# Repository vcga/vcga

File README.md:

UNTUK SAAT INI HINGGA JANGKA WAKTU YANG BELUM DAPAT DITENTUKAN,
BAHWASANYA VCGA SEBAGAI ANAK CABANG DARI DARI MATRIX 1.4 III,
DALAM MASA "SUSPENDED"
ATAU "DITUTUP SEMENTARA" TERKAIT MASA "SUSPENDED" YANG DIPERLAKUKAN
TERHADAP KESELURUHAN MATRIX 1.4. PENYEDIAAN DUKUNGAN TEKNIKAL, SKEMATIK,
& DOKUMENTASI - DIHENTIKAN.
SKEMATIK & DOKUMENTASI LAINNYA AKAN TERSEDIA KEMBALI JIKA TELAH
DIPUTUSKAN KEADAAN "DIBUKA KEMBALI".

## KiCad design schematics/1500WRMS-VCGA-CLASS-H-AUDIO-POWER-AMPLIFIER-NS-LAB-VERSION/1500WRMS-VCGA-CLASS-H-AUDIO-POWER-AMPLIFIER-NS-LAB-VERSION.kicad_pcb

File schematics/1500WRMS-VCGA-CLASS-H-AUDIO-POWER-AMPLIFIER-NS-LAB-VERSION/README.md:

1500 Watt RMS MATRIX 1.4 III Class-H Audio Power Amplifier Core Circuit
=======================================================================

BASIC TECHNICAL SPECIFICATIONS
------------------------------

Output Power Rating: 1500 watts RMS  
Output Amplitude Rating: 78.4V RMS  
Minimum Output Load Impedance: 4-ohms  
High Rail Power Supply Voltage: 120V DC precision dual-supply  
Low Rail Power Supply Voltage: 42V DC precision dual-supply  
Input: 1V RMS nominal, 10V RMS maximum  

Features:
- Stepper Frequency Limiter to prevent distortion of high frequency amplification
- Soft Signal Limiter
- Fault / Short & Open Circuit Protection

ACKNOWLEDGMENT
--------------

This model contains contributed bug fixing of signal-limiter over-peak detector
circuit by [MATRIX 1.4 III](https://github.com/kicader/MATRIX-1.4-III)
Development Team.

ANALYSIS NOTE
------------------

The schematic package include SPICE netlist that may not compatible
with certain SPICE simulator. It has been tested only with use NGSPICE V.30,
and known incompatible with SPICE-OPUS.

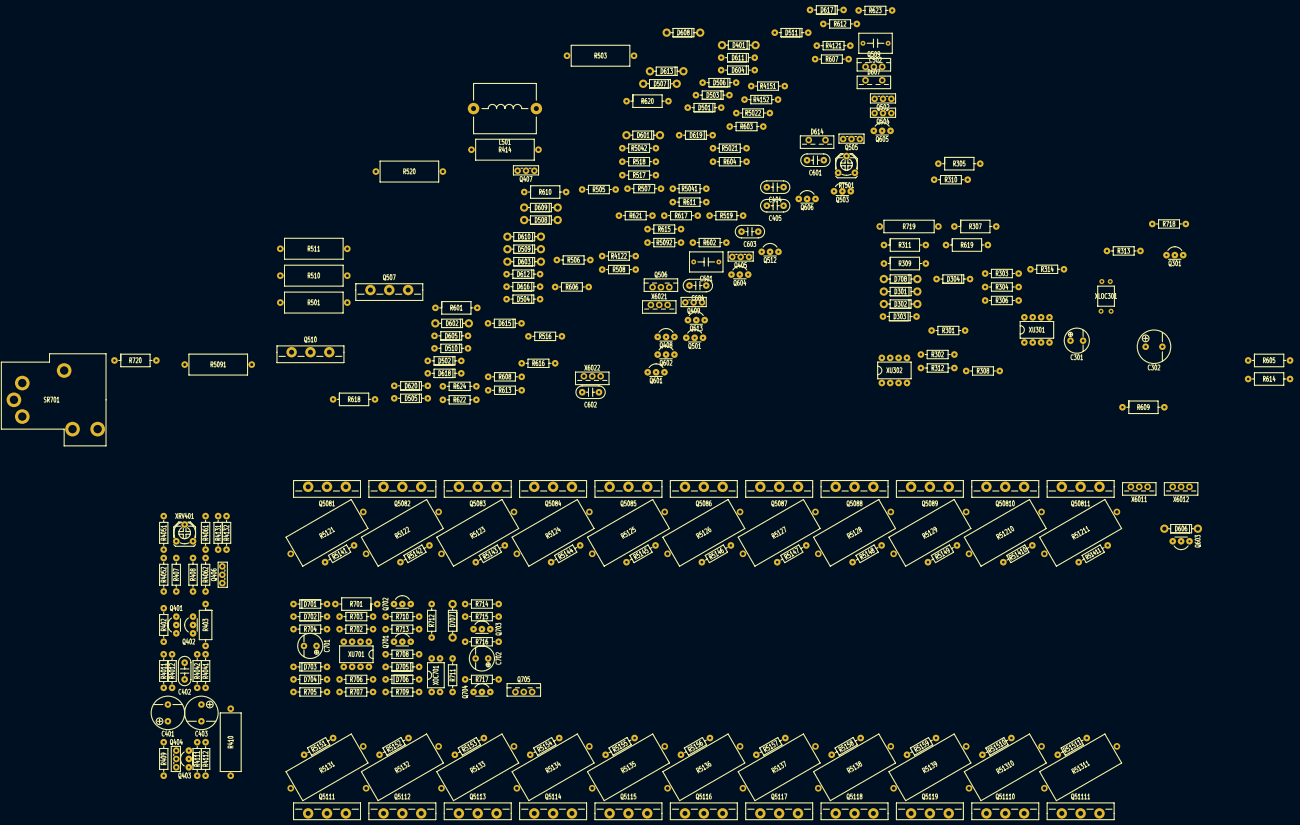
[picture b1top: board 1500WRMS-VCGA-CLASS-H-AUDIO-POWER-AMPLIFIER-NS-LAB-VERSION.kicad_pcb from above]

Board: 2 copper layers, 270 parts (0 on the bottom side), 142 nets, no tracks yet.

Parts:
C301, C702: 10uF; CAPACITOR_AE_D7.62mm
C302, C401, C403: 220uF; CAPACITOR_AE_D10mm
C402: 470pF; CAPACITOR_CERAMIC_STD
C404, C405: 120pF; CAPACITOR_CERAMIC_STD
C501, C502: 0.1uF; CAPACITOR_MPF_STD
C601, C602: 0.1uF; CAPACITOR_CERAMIC_STD
C603, C604: 6.8nF; CAPACITOR_CERAMIC_STD
C701: 1uF; CAPACITOR_AE_D7.62mm
D301, D302, D601, D608: 1N4738; DIODE_AXIAL_SMALL_SI
D303, D304, D501, D502, D503, D504, D505, D506, D510, D511, D604, D605, D611, D612, D615, D616, D617, D618, D619, D620, D701, D702, D703, D704, D705, D706: 1N4148; DIODE_AXIAL_SMALL_GE
D401, D507, D508, D509, D602, D609: 1N4004; DIODE_AXIAL_SMALL_SI
D603, D610: 1N4007; DIODE_AXIAL_SMALL_SI
D606, D613: 1N4742; DIODE_AXIAL_SMALL_SI
D607, D614: MURF1560; DIODE_POWER_TO-220AC-MIRRORED
D707: 1N4732; DIODE_AXIAL_SMALL_SI
D708: 1N4002; DIODE_AXIAL_SMALL_SI
L501: 3uH; INDUCTOR_AIR_CORE_3uH_D600mils_L750mils
Q301, Q401, Q402, Q403, Q408, Q503, Q512, Q601, Q605, Q606, Q701, Q703, Q704: 2N5551; TO-92-EBC
Q404, Q409, Q504, Q505: MJE340; TO-225
Q405, Q406, Q407, Q502: MJE350; TO-225
Q501, Q513, Q602, Q603, Q604, Q702: 2N5401; TO-92-EBC
Q506: MJE15032; TO-220
Q507, Q5081, Q5082, Q5083, Q5084, Q5085, Q5086, Q5087, Q5088, Q5089, Q50810, Q50811: 2SC5200; TO-264-MIRRORED
Q509: MJE15033; TO-220
Q510, Q5111, Q5112, Q5113, Q5114, Q5115, Q5116, Q5117, Q5118, Q5119, Q51110, Q51111: 2SA1943; TO-264-MIRRORED
Q705: TIP42C; TO-220
R301, R702: 100k; RESISTOR_AXIAL_0.25W
R302: 3.3k; RESISTOR_AXIAL_0.25W
R303, R703, R711: 1k; RESISTOR_AXIAL_0.25W
R304: 180k; RESISTOR_AXIAL_0.25W
R305, R307, R309, R311, R701, R720: 100k; RESISTOR_AXIAL_0.5W
R306, R308, R310, R312, R314, R708, R709, R710, R712, R5092: 2.7k; RESISTOR_AXIAL_0.25W
R313, R603, R604, R612, R613, R714: 15k; RESISTOR_AXIAL_0.25W
R402: 22k; RESISTOR_AXIAL_0.25W
R403: 22k; RESISTOR_AXIAL_0.5W
R407, R408, R717: 5.6k; RESISTOR_AXIAL_0.25W
R409: 270; RESISTOR_AXIAL_0.25W
R410, R414, R501, R503: 22k; RESISTOR_AXIAL_2W
R505, R517, R519: 820; RESISTOR_AXIAL_0.25W
R506: 1.2k; RESISTOR_AXIAL_0.25W
R507, R704, R4012, R4042: 4.7k; RESISTOR_AXIAL_0.25W
R508: 180; RESISTOR_AXIAL_0.25W
R510, R511: 12; RESISTOR_AXIAL_2W
R516, R518, R706, R707: 10k; RESISTOR_AXIAL_0.25W
R520: 10; RESISTOR_AXIAL_2W
R601, R610, R619, R620: 47k; RESISTOR_AXIAL_0.5W
R602, R611: 33k; RESISTOR_AXIAL_0.25W
R605, R614: 68k; RESISTOR_AXIAL_0.5W
R606, R615, R718: 3.9k; RESISTOR_AXIAL_0.25W
R607, R616: 20k; RESISTOR_AXIAL_0.25W
R608, R617: 220; RESISTOR_AXIAL_0.25W
R609, R618: 20k; RESISTOR_AXIAL_0.5W
R621, R623, R715: 12k; RESISTOR_AXIAL_0.25W
R622, R624: 47k; RESISTOR_AXIAL_0.25W
R705: 120k; RESISTOR_AXIAL_0.25W
R713: 2.2k; RESISTOR_AXIAL_0.25W
R716: 82k; RESISTOR_AXIAL_0.25W
R719: 150; RESISTOR_AXIAL_1W
R4011: 330; RESISTOR_AXIAL_0.25W
R4041: 300; RESISTOR_AXIAL_0.25W
R4051, R4061: 470; RESISTOR_AXIAL_0.25W
R4052, R4062: 22; RESISTOR_AXIAL_0.25W
R4111, R4121, R4131, R4151, R5021, R5041: 150; RESISTOR_AXIAL_0.25W
R4112, R5022, R5042: 680; RESISTOR_AXIAL_0.25W
R4122, R4132, R4152: 750; RESISTOR_AXIAL_0.25W
R5091: 120; RESISTOR_AXIAL_2W
R5121, R5122, R5123, R5124, R5125, R5126, R5127, R5128, R5129, R5131, R5132, R5133, R5134, R5135, R5136, R5137, R5138, R5139, R51210, R51211, R51310, R51311: 0.56; RESISTOR_BLOCK_5W
R5141, R5142, R5143, R5144, R5145, R5146, R5147, R5148, R5149, R5151, R5152, R5153, R5154, R5155, R5156, R5157, R5158, R5159, R51410, R51411, R51510, R51511: 100; RESISTOR_AXIAL_0.25W
RT501: 5k; RESISTOR_ROUND_TRIMPOT_STD
SR701: sw1 ON; RL-SLA24
X6011, X6012: IRF9540; TO-220-MIRRORED
X6021, X6022: IRF540; TO-220-MIRRORED
XLOC301: NSL32
XOC701: PC817; DIP4
XRV401: VR; RESISTOR_ROUND_TRIMPOT_STD
XU301, XU302, XU701: JRC4558; DIP8

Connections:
0: C302.2, C402.1, C403.2, C502.2, C701.2, C702.2, D304.1, D401.1, D701.2, D702.1, D703.2, D704.1, Q301.3, Q703.3, R301.2, R304.2, R306.2, R308.2, R310.2, R312.2, R402.2, R410.1, R501.2, R503.1, R703.2, R707.2, R708.1, R709.2, R715.2, R717.2, R720.2, XLOC301.4, XOC701.3
+15V: Q702.3, Q705.3, R314.1, R713.1, R716.1, R718.1, XU301.8, XU302.8, XU701.8
+42V: D605.1, D607.1, D616.1, Q601.3, R602.2, R605.2, R609.2, R621.1
+120V: D301.2, D606.2, Q501.3, Q602.3, Q603.3, R601.1, R603.1, R4051.1, R4061.1, R4121.1, R4122.1, R4131.1, R4132.1, R5021.1, R5022.1, X6011.3, X6012.3, XRV401.2
-15V: R719.2, XU301.4, XU302.4, XU701.4
-42V: D612.2, D614.2, D619.2, Q604.3, R611.1, R614.1, R618.1, R623.1
-120V: D302.1, D613.1, Q403.3, Q408.3, Q503.3, Q605.3, Q606.3, R414.2, R610.2, R612.2, R4111.2, R4112.2, R4151.2, R4152.2, R5041.2, R5042.2, X6021.3, X6022.3
/+RLC: D708.2, Q705.1, SR701.3
/-RLC: D708.1, R719.1, SR701.4
/M_DRV1N: Q509.3, Q510.2, R5091.2, R5092.2
/M_DRV1P: Q506.3, Q507.2, R5091.1, R5092.1
/M_DRV2N: Q510.3, Q5111.2, Q5112.2, Q5113.2, Q5114.2, Q5115.2, Q5116.2, Q5117.2, Q5118.2, Q5119.2, Q51110.2, Q51111.2, R511.2
/M_DRV2P: Q507.3, Q5081.2, Q5082.2, Q5083.2, Q5084.2, Q5085.2, Q5086.2, Q5087.2, Q5088.2, Q5089.2, Q50810.2, Q50811.2, R510.1
/M_FPODLO: D703.1, D704.2, R704.2, R705.1
/M_FPODO: D705.1, D706.2, R706.1, XU701.7
/M_FPSO: Q703.2, R714.2, R715.1
/M_FPSSN: R518.2, R5151.1, R5152.1, R5153.1, R5154.1, R5155.1, R5156.1, R5157.1, R5158.1, R5159.1, R51510.1, R51511.1, XOC701.2
/M_FPSSP: D707.2, R516.2, R5141.2, R5142.2, R5143.2, R5144.2, R5145.2, R5146.2, R5147.2, R5148.2, R5149.2, R51410.2, R51411.2
/M_FPTH: C702.1, Q703.1, Q704.2, R716.2
/M_LMSON: D303.2, XU302.1
/M_LMSOP: R313.1, XU302.7
/M_NFB: Q402.2, R403.2, R4041.2, R4042.2
/M_OUT_RAW: D601.1, D608.2, L501.1, Q512.3, Q513.3, R305.1, R309.1, R403.1, R510.2, R511.1, R517.1, R519.1, R520.1, R701.1, R5121.2, R5122.2, R5123.2, R5124.2, R5125.2, R5126.2, R5127.2, R5128.2, R5129.2, R5131.1, R5132.1, R5133.1, R5134.1, R5135.1, R5136.1, R5137.1, R5138.1, R5139.1, R51210.2, R51211.2, R51310.1, R51311.1
/M_REF: C402.2, Q401.2, R402.1, R4011.1, R4012.1
/M_VASIOUT: C405.2, Q406.1, Q407.3
/M_VASOUT: C404.2, D503.2, D504.1, Q405.1, Q409.1
/M_VBIASN: C501.2, D506.2, D507.2, D509.2, D511.2, Q504.1, Q509.2
/M_VBIASP: C501.1, D501.1, D508.1, D510.1, Q502.1, Q505.1, Q506.2, R505.1
/M_VSWOP: D508.2, D607.2, D615.1, Q506.1, Q507.1, Q5081.1, Q5082.1, Q5083.1, Q5084.1, Q5085.1, Q5086.1, Q5087.1, Q5088.1, Q5089.1, Q50810.1, Q50811.1, R619.2, X6011.1, X6012.1
JH1: C604.1, D618.1, R620.2
LIMIT_IND_SRC: C302.1, Q301.1, XLOC301.2
M_VSWON: D509.1, D614.1, D618.2, Q509.1, Q510.1, Q5111.1, Q5112.1, Q5113.1, Q5114.1, Q5115.1, Q5116.1, Q5117.1, Q5118.1, Q5119.1, Q51110.1, Q51111.1, R619.1, X6021.1, X6022.1
unnamed: C301.2, R301.1, XU301.3
unnamed: C401.1, R303.1, XU301.7
unnamed: C401.2, R4011.2, R4012.2
unnamed: C403.1, R4041.1, R4042.1
unnamed: C404.1, Q401.1, Q405.2, R407.2, R4052.2
unnamed: C405.1, Q402.1, Q406.2, R408.2, R4062.2
unnamed: C502.1, R520.2
unnamed: C601.1, D604.1, R607.2
unnamed: C601.2, D605.2, R608.2
unnamed: C602.1, D611.2, R616.1
unnamed: C602.2, D612.1, R617.1
unnamed: C603.1, D615.2, R620.1
unnamed: C603.2, D616.2, D617.1, R621.2
unnamed: C604.2, D619.1, D620.2, R623.2
unnamed: C701.1, R705.2, XU701.5
unnamed: D301.1, R307.1
unnamed: D302.2, R311.1
unnamed: D303.1, R307.2, R308.1, XU302.6
unnamed: D304.2, Q301.2, R313.2
unnamed: D401.2, Q407.2, R414.1
unnamed: D501.2, D502.1
unnamed: D502.2, D503.1
unnamed: D504.2, D505.1
unnamed: D505.2, D506.1
unnamed: D507.1, R506.2, R508.2, RT501.2
unnamed: D510.2, Q512.1
unnamed: D511.1, Q513.1
unnamed: D601.2, D602.2
unnamed: D602.1, D603.1, R601.2
unnamed: D603.2, Q601.2, R602.1, R622.2
unnamed: D604.2, Q601.1, R603.2, R604.1
unnamed: D606.1, Q603.1, R607.1, R608.1, R609.1, X6011.2, X6012.2
unnamed: D608.1, D609.1
unnamed: D609.2, D610.2, R610.1
unnamed: D610.1, Q604.2, R611.2, R624.2
unnamed: D611.1, Q604.1, R612.1, R613.1
unnamed: D613.2, Q606.1, R616.2, R617.2, R618.2, X6021.2, X6022.2
unnamed: D617.2, R622.1
unnamed: D620.1, R624.1
unnamed: D701.1, D702.2, R701.2, XU701.3
unnamed: D705.2, Q701.2, R708.2
unnamed: D706.1, Q701.3, R709.1
unnamed: D707.1, R711.1
unnamed: L501.2, R720.1, SR701.1
unnamed: Q401.3, Q402.3, R409.1
unnamed: Q403.1, Q404.2, R410.2
unnamed: Q403.2, Q404.3, R4111.1, R4112.1
unnamed: Q404.1, R409.2
unnamed: Q405.3, R4121.2, R4122.2
unnamed: Q406.3, R4131.2, R4132.2
unnamed: Q407.1, Q408.1, Q409.2
unnamed: Q408.2, Q409.3, R4151.1, R4152.1
unnamed: Q501.1, Q502.2, R501.1
unnamed: Q501.2, Q502.3, R5021.2, R5022.2
unnamed: Q503.1, Q504.2, R503.2
unnamed: Q503.2, Q504.3, R5041.1, R5042.1
unnamed: Q505.2, R505.2, R506.1, R507.1
unnamed: Q505.3, R508.1
unnamed: Q512.2, R516.1, R517.2
unnamed: Q513.2, R518.1, R519.2
unnamed: Q602.1, R605.1, R606.1
unnamed: Q602.2, R604.2
unnamed: Q603.2, R606.2
unnamed: Q605.1, R614.2, R615.1
unnamed: Q605.2, R613.2
unnamed: Q606.2, R615.2
unnamed: Q701.1, R710.1
unnamed: Q702.1, R714.1
unnamed: Q702.2, R710.2, R712.1, R713.2
unnamed: Q704.1, Q705.2, R718.2
unnamed: Q704.3, R717.1
unnamed: Q5081.3, R5121.1, R5141.1
unnamed: Q5082.3, R5122.1, R5142.1
unnamed: Q5083.3, R5123.1, R5143.1
unnamed: Q5084.3, R5124.1, R5144.1
unnamed: Q5085.3, R5125.1, R5145.1
unnamed: Q5086.3, R5126.1, R5146.1
unnamed: Q5087.3, R5127.1, R5147.1
unnamed: Q5088.3, R5128.1, R5148.1
unnamed: Q5089.3, R5129.1, R5149.1
unnamed: Q5111.3, R5131.2, R5151.2
unnamed: Q5112.3, R5132.2, R5152.2
unnamed: Q5113.3, R5133.2, R5153.2
unnamed: Q5114.3, R5134.2, R5154.2
unnamed: Q5115.3, R5135.2, R5155.2
unnamed: Q5116.3, R5136.2, R5156.2
unnamed: Q5117.3, R5137.2, R5157.2
unnamed: Q5118.3, R5138.2, R5158.2
unnamed: Q5119.3, R5139.2, R5159.2
unnamed: Q50810.3, R51210.1, R51410.1
unnamed: Q50811.3, R51211.1, R51411.1
unnamed: Q51110.3, R51310.2, R51510.2
unnamed: Q51111.3, R51311.2, R51511.2
unnamed: R302.1, XU301.1, XU301.2
unnamed: R302.2, XLOC301.3, XU301.5
unnamed: R303.2, R304.1, XU301.6
unnamed: R305.2, R306.1, XU302.5
unnamed: R309.2, R310.1, XU302.3
unnamed: R311.2, R312.1, XU302.2
unnamed: R314.2, XLOC301.1
unnamed: R407.1, XRV401.1
unnamed: R408.1, XRV401.3
unnamed: R507.2, RT501.1
unnamed: R702.1, R704.1, XU701.1
unnamed: R702.2, R703.1, XU701.2
unnamed: R706.2, R707.1, XU701.6
unnamed: R711.2, XOC701.1
unnamed: R712.2, XOC701.4
unnamed: R4051.2, R4052.1
unnamed: R4061.2, R4062.1

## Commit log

2019-05-03 Commit Fri May 3 11:49:36 UTC 2019
2019-05-03 Commit Fri May 3 11:54:26 UTC 2019
2019-05-03 Commit Fri May 3 11:57:45 UTC 2019
2019-05-03 Commit Fri May 3 13:10:42 UTC 2019
2019-05-03 Commit Fri May 3 13:12:31 UTC 2019
2019-05-03 Commit Fri May 3 13:21:25 UTC 2019
2019-05-03 Commit Fri May 3 13:25:26 UTC 2019
2019-05-03 Commit Fri May 3 13:58:15 UTC 2019
2019-05-03 Commit Fri May 3 14:08:18 UTC 2019
2019-05-03 Commit Fri May 3 15:21:50 UTC 2019
2019-05-03 Commit Fri May 3 19:32:53 UTC 2019
2019-05-08 Commit Wed May 8 11:35:14 UTC 2019
2019-05-08 Commit Wed May 8 12:11:19 UTC 2019
2019-05-08 Commit Wed May 8 12:20:54 UTC 2019
2019-05-09 Commit Thu May 9 11:52:12 UTC 2019
2019-05-09 Commit Thu May 9 13:03:28 UTC 2019
2019-05-13 Commit Mon May 13 03:19:53 UTC 2019
2019-05-13 Commit Mon May 13 03:59:59 UTC 2019
2019-05-13 Commit Mon May 13 04:01:48 UTC 2019
2019-05-15 Commit Wed May 15 20:03:55 UTC 2019
2019-05-15 Commit Wed May 15 20:10:59 UTC 2019
2019-05-15 Commit Wed May 15 20:21:28 UTC 2019
2019-05-15 Commit Wed May 15 20:44:50 UTC 2019
2019-06-28 Commit Fri Jun 28 05:46:59 UTC 2019
